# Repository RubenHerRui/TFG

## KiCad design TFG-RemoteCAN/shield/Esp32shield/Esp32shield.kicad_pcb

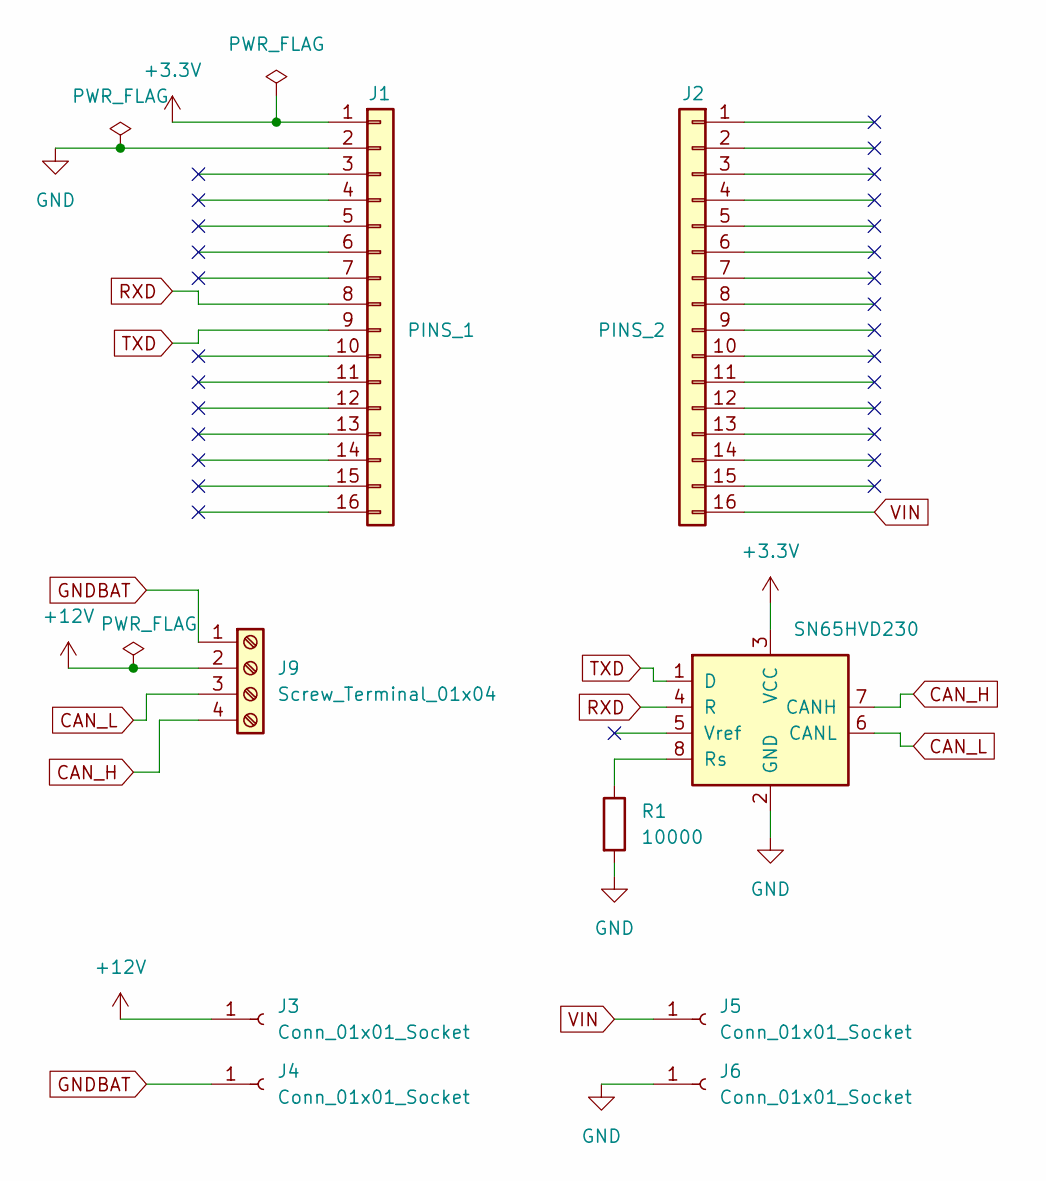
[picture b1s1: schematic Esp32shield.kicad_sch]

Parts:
J1: PINS_1; PinSocket_1x16_P2.54mm_Vertical
J2: PINS_2; PinSocket_1x16_P2.54mm_Vertical
J3, J4, J5, J6: Conn_01x01_Socket; MountingHole_2.2mm_M2_DIN965_Pad
J9: Screw_Terminal_01x04; TerminalBlock_Phoenix_MPT-0,5-4-2.54_1x04_P2.54mm_Horizontal
R1: 10000; R_Axial_DIN0207_L6.3mm_D2.5mm_P7.62mm_Horizontal
U1: SN65HVD230; SOIC-8_3.9x4.9mm_P1.27mm

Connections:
+3.3V: J1.1, U1.3 (VCC)
+12V: J3.1, J9.2
CAN_H: J9.4, U1.7 (CANH)
CAN_L: J9.3, U1.6 (CANL)
GND: J1.2, J6.1, R1.2, U1.2 (GND)
GNDBAT: J4.1, J9.1
unnamed: R1.1, U1.8 (Rs)
RXD: J1.8, U1.4 (R)
TXD: J1.9, U1.1 (D)
VIN: J2.16, J5.1

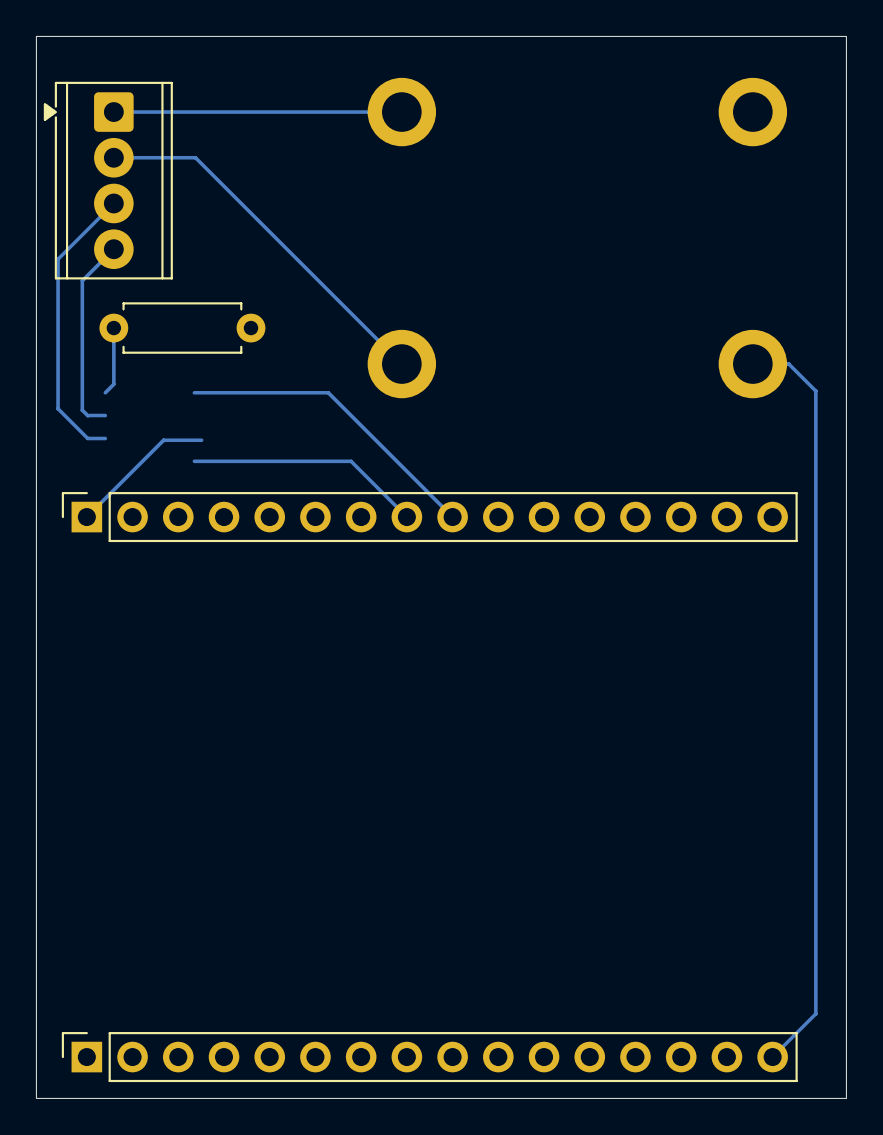
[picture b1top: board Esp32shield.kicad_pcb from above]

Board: 2 copper layers, 45.0 x 59.0 mm, 9 parts (1 on the bottom side), 10 nets.

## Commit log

2025-03-25 V0.1
2025-04-14 Versió 0.2
2025-06-03 Versió 1.0
2025-07-04 Versió 1.1
